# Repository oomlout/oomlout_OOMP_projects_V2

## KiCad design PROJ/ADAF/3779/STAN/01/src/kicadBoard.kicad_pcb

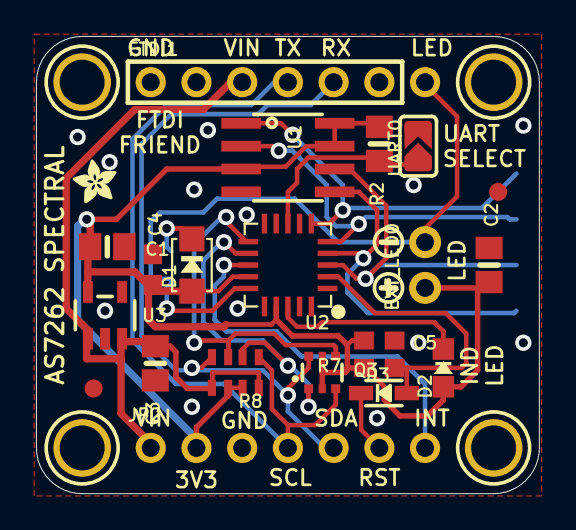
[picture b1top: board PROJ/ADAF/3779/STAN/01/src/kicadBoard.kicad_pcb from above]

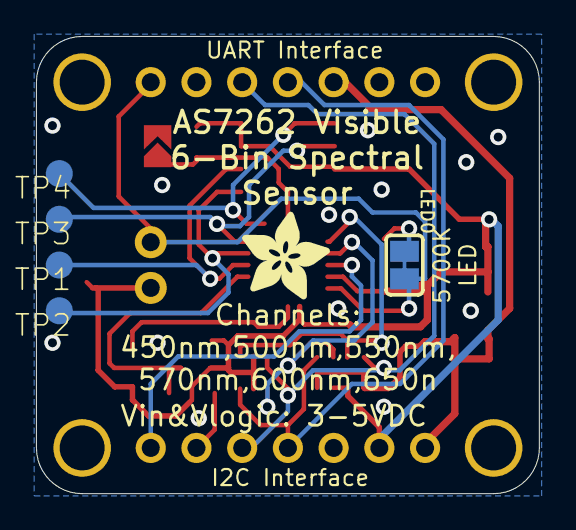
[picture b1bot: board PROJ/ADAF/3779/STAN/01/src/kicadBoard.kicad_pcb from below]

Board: 2 copper layers, 27.9 x 25.4 mm, 34 parts (6 on the bottom side), 18 nets.

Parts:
C1, C2, C3: 10uF; 0805-NO
C4, C5: 0.1uF; 0603-NO
D1: L130-5780001400001; EVERLIGHT_45-21
D2: GREEN; CHIPLED_0805_NOOUTLINE
D3: IN4148; SOD-323
EXT_LED0: 1X02_ROUND
FID2, FID3: FIDUCIAL_1MM
FTDI1: 1X07_ROUND
JP2: 1X07_ROUND
LED0: SOLDERJUMPER_CLOSEDWIRE
Q3: BSS138; SOT363
R2: 10K; 0805-NO
R7: 10K; 0603-NO
R8: 10k; RESPACK_4X0603_NO
TP1, TP2, TP3, TP4: PTR1TP15R; TP15R
U1: AT25SF041-SSHD-B; SOIC8_150MIL
U2: AS7262-BLGT; AS726X_LGA20
U3: MIC5225-3.3; SOT23-5
U$2, U$3, U$22, U$23: MOUNTINGHOLE2.5; MOUNTINGHOLE_2.5_PLATED
U$9: ADAFRUIT_5MM
U$21: ADAFRUIT_2.5MM
U$25: SYMBOL_PLUS
U$26: SYMBOL_MINUS
UART0: SOLDERJUMPER_ARROW_NOPASTE

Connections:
3.3V: C1.1, C2.1, C4.1, C5.1, D1.A, D2.A, EXT_LED0.1, JP2.2, Q3.2, Q3.5, R2.1, R7.2, R8.6, R8.7, U1.3, U1.7, U1.8, U2.14, U2.17, U3.5
BUS_3V: R2.2, U2.8, UART0.1
GND: C1.2, C2.2, C3.2, C4.2, C5.2, FTDI1.1, JP2.3, U1.4, U2.16, U3.2, UART0.2
IND: D2.C, U2.18
INT: JP2.7, U2.13
LED: EXT_LED0.2, FTDI1.7, LED0.2, U2.15
unnamed: D1.K, LED0.1
RESET: D3.C, JP2.6
RST_3V: D3.A, R7.1, U2.2
RX/SCL: FTDI1.4, JP2.4, Q3.3, R8.1
RX/SCL_3V: Q3.4, R8.3, U2.11
SPIF_CS: TP4.TP, U1.1, U2.6
SPIF_MISO: TP3.TP, U1.2, U2.5
SPIF_MOSI: TP2.TP, U1.5, U2.4
SPIF_SCK: TP1.TP, U1.6, U2.3
TX/SDA: FTDI1.5, JP2.5, Q3.6, R8.4
TX/SDA_3V: Q3.1, R8.2, U2.12
VIN: C3.1, FTDI1.3, JP2.1, R8.5, R8.8, U3.1, U3.3

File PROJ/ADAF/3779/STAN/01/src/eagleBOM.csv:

"Part";"Value";"Device";"Package";"Description";"BOM";"TP_SIGNAL_NAME";
"C1";"10uF";"RESISTOR0805_NOOUTLINE";"0805-NO";"Resistors";"";"";
"C2";"10uF";"CAP_CERAMIC0805-NOOUTLINE";"0805-NO";"Ceramic Capacitors";"";"";
"C3";"10uF";"CAP_CERAMIC0805-NOOUTLINE";"0805-NO";"Ceramic Capacitors";"";"";
"C4";"0.1uF";"CAP_CERAMIC0603_NO";"0603-NO";"Ceramic Capacitors";"";"";
"C5";"0.1uF";"CAP_CERAMIC0603_NO";"0603-NO";"Ceramic Capacitors";"";"";
"D1";"L130-5780001400001";"LEDEV45-21";"EVERLIGHT_45-21";"LED";"";"";
"D2";"GREEN";"LED0805_NOOUTLINE";"CHIPLED_0805_NOOUTLINE";"LED";"";"";
"D3";"IN4148";"DIODESOD-323";"SOD-323";"Diode";"";"";
"EXT_LED";"";"HEADER-1X2ROUND";"1X02_ROUND";"PIN HEADER";"";"";
"FID2";"FIDUCIAL_1MM";"FIDUCIAL_1MM";"FIDUCIAL_1MM";"Fiducial Alignment Points";"EXCLUDE";"";
"FID3";"FIDUCIAL_1MM";"FIDUCIAL_1MM";"FIDUCIAL_1MM";"Fiducial Alignment Points";"EXCLUDE";"";
"FTDI1";"";"HEADER-1X7ROUND";"1X07_ROUND";"PIN HEADER";"";"";
"JP2";"";"HEADER-1X7ROUND";"1X07_ROUND";"PIN HEADER";"";"";
"LED";"";"SOLDERJUMPERCLOSED";"SOLDERJUMPER_CLOSEDWIRE";"SMD Solder JUMPER";"";"";
"Q3";"BSS138";"MOSFET-N_DUAL";"SOT363";"Dual N-Channel MOSFET";"";"";
"R2";"10K";"RESISTOR0805_NOOUTLINE";"0805-NO";"Resistors";"";"";
"R7";"10K";"RESISTOR_0603_NOOUT";"0603-NO";"Resistors";"";"";
"R8";"10k";"RESISTOR_4PACK_NO";"RESPACK_4X0603_NO";"Resistor Packs (4 resistors)";"";"";
"TP1";"PTR1TP15R";"PTR1TP15R";"TP15R";"TEST PIN";"";"";
"TP2";"PTR1TP15R";"PTR1TP15R";"TP15R";"TEST PIN";"";"";
"TP3";"PTR1TP15R";"PTR1TP15R";"TP15R";"TEST PIN";"";"";
"TP4";"PTR1TP15R";"PTR1TP15R";"TP15R";"TEST PIN";"";"";
"U$2";"MOUNTINGHOLE2.5";"MOUNTINGHOLE2.5";"MOUNTINGHOLE_2.5_PLATED";"Mounting Hole";"EXCLUDE";"";
"U$3";"MOUNTINGHOLE2.5";"MOUNTINGHOLE2.5";"MOUNTINGHOLE_2.5_PLATED";"Mounting Hole";"EXCLUDE";"";
"U$22";"MOUNTINGHOLE2.5";"MOUNTINGHOLE2.5";"MOUNTINGHOLE_2.5_PLATED";"Mounting Hole";"EXCLUDE";"";
"U$23";"MOUNTINGHOLE2.5";"MOUNTINGHOLE2.5";"MOUNTINGHOLE_2.5_PLATED";"Mounting Hole";"EXCLUDE";"";
"U1";"AT25SF041-SSHD-B";"SPIFLASH_SOIC8";"SOIC8_150MIL";"SOIC8 SPI Flash";"";"";
"U2";"AS7262-BLGT";"AS726X_SPECTRAL";"AS726X_LGA20";"AS726x Spectral Sensor";"";"";
"U3";"MIC5225-3.3";"VREG_SOT23-5";"SOT23-5";"SOT23-5 Fixed Voltage Regulators";"";"";
"UART";"";"SOLDERJUMPER";"SOLDERJUMPER_ARROW_NOPASTE";"SMD Solder JUMPER";"EXCLUDE";"";

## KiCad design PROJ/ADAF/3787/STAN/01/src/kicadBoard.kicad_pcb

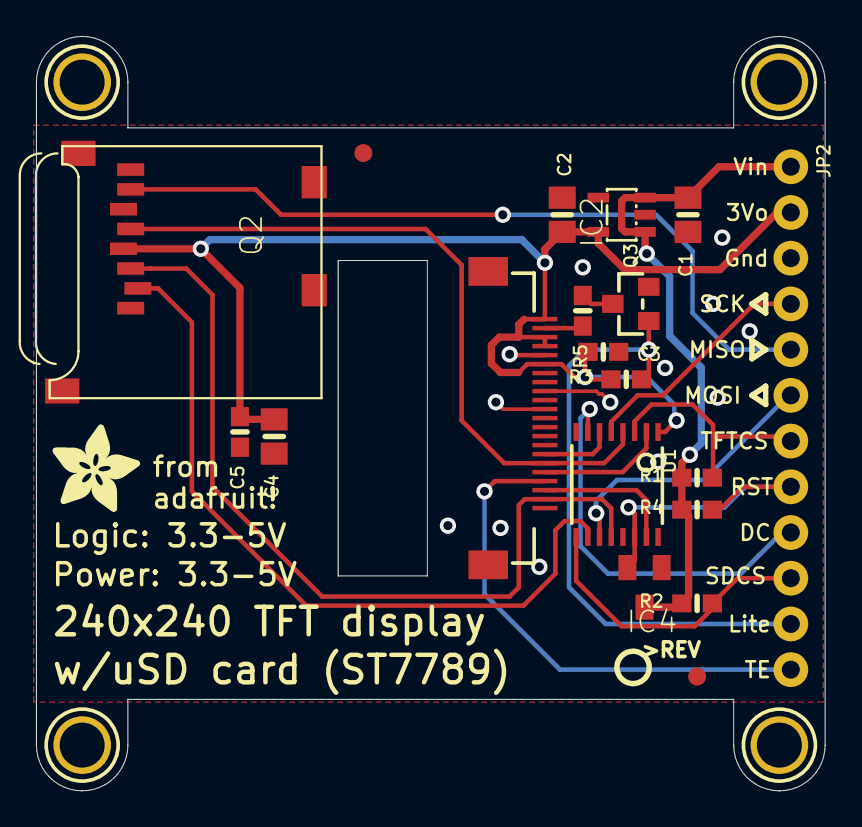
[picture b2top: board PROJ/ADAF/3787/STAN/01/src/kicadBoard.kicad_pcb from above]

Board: 16 copper layers, 43.8 x 41.9 mm, 25 parts (1 on the bottom side), 20 nets.

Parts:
C1, C2, C4: 10uF; 0805-NO
C3, C5: 0.1uF; 0603-NO
IC2: AP2112; SOT23-5L
IC4: APX803-SAG; SOT23
JP2: 1X12_ROUND_76MIL
Q2: MICROSD
Q3: BSS138; SOT23-WIDE
R1, R2, R3, R4: 10K; 0603-NO
R5: 10; 0603-NO
TFT1: DISP_TFT_1.54IN_240X240_22P; TFT_1.54IN_240X240_22PIN
U1: 74HC4050PWR; TSSOP16
U$1: ADAFRUIT_5MM
U$2: PCBFEAT-REV-040
U$4, U$5: FIDUCIAL_1MM
U$7, U$8, U$9, U$10: MOUNTINGHOLE2.5; MOUNTINGHOLE_2.5_PLATED

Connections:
+3V3: C2.1, C3.1, C4.1, C5.1, IC2.5, JP2.2, Q2.4, R3.2, TFT1.1, TFT1.3, TFT1.4, TFT1.6, U1.1
CARDCS: JP2.10, R2.1, U1.9
CARDCS_3V: Q2.2, U1.10
GND: C1.2, C2.2, C3.2, C4.2, C5.2, IC2.2, IC4.1, JP2.3, Q2.6, Q2.MT1, Q2.MT2, Q3.2, TFT1.5, TFT1.7, TFT1.8, TFT1.9, TFT1.10, TFT1.11, TFT1.12, TFT1.13, TFT1.14, TFT1.15, TFT1.22, TFT1.SUPPORT1, TFT1.SUPPORT2, U1.8
LEDK: R5.2, TFT1.2
LITE: JP2.11, Q3.1, R3.1
MISO: JP2.5, Q2.7
MOSI: JP2.6, U1.11
MOSI_3V: Q2.3, TFT1.21, U1.12
unnamed: Q3.3, R5.1
SCK: JP2.4, U1.5
SCK_3V: Q2.5, TFT1.17, U1.4
TE: JP2.12, TFT1.19
TFTCS: JP2.7, R1.1, U1.3
TFTCS_3V: TFT1.18, U1.2
TFTDC: JP2.9, U1.7
TFTDC_3V: TFT1.16, U1.6
TFTRST: IC4.2, JP2.8, R4.1, U1.14
TFTRST_3V: TFT1.20, U1.15
VIN: C1.1, IC2.1, IC2.3, IC4.3, JP2.1, R1.2, R2.2, R4.2

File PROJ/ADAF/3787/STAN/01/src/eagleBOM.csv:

"Part";"Value";"Device";"Package";"Description";"BOM";
"C1";"10uF";"CAP_CERAMIC0805-NOOUTLINE";"0805-NO";"Ceramic Capacitors";"";
"C2";"10uF";"CAP_CERAMIC0805-NOOUTLINE";"0805-NO";"Ceramic Capacitors";"";
"C3";"0.1uF";"CAP_CERAMIC0603_NO";"0603-NO";"Ceramic Capacitors";"";
"C4";"10uF";"CAP_CERAMIC0805-NOOUTLINE";"0805-NO";"Ceramic Capacitors";"";
"C5";"0.1uF";"CAP_CERAMIC0603_NO";"0603-NO";"Ceramic Capacitors";"";
"IC2";"AP2112";"LP298XS";"SOT23-5L";"";"";
"IC4";"APX803-SAG";"AXP083-SAG";"SOT23";"";"";
"JP2";"";"HEADER-1X1276MIL";"1X12_ROUND_76MIL";"";"";
"Q2";"MICROSD";"MICROSD";"MICROSD";"Micro-SD / Transflash card holder with SPI pinout";"";
"Q3";"BSS138";"MOSFET-NWIDE";"SOT23-WIDE";"N-Channel Mosfet";"";
"R1";"10K";"RESISTOR_0603_NOOUT";"0603-NO";"Resistors";"";
"R2";"10K";"RESISTOR_0603_NOOUT";"0603-NO";"Resistors";"";
"R3";"10K";"RESISTOR_0603_NOOUT";"0603-NO";"Resistors";"";
"R4";"10K";"RESISTOR_0603_NOOUT";"0603-NO";"Resistors";"";
"R5";"10";"RESISTOR_0603_NOOUT";"0603-NO";"Resistors";"";
"TFT1";"DISP_TFT_1.54IN_240X240_22P";"DISP_TFT_1.54IN_240X240_22P";"TFT_1.54IN_240X240_22PIN";"";"";
"U$4";"FIDUCIAL_1MM";"FIDUCIAL_1MM";"FIDUCIAL_1MM";"Fiducial Alignment Points";"EXCLUDE";
"U$5";"FIDUCIAL_1MM";"FIDUCIAL_1MM";"FIDUCIAL_1MM";"Fiducial Alignment Points";"EXCLUDE";
"U$7";"MOUNTINGHOLE2.5";"MOUNTINGHOLE2.5";"MOUNTINGHOLE_2.5_PLATED";"Mounting Hole";"EXCLUDE";
"U$8";"MOUNTINGHOLE2.5";"MOUNTINGHOLE2.5";"MOUNTINGHOLE_2.5_PLATED";"Mounting Hole";"EXCLUDE";
"U$9";"MOUNTINGHOLE2.5";"MOUNTINGHOLE2.5";"MOUNTINGHOLE_2.5_PLATED";"Mounting Hole";"EXCLUDE";
"U$10";"MOUNTINGHOLE2.5";"MOUNTINGHOLE2.5";"MOUNTINGHOLE_2.5_PLATED";"Mounting Hole";"EXCLUDE";
"U1";"74HC4050PWR";"74HC4050DTSSOP";"TSSOP16";"6-channel level shifter";"";

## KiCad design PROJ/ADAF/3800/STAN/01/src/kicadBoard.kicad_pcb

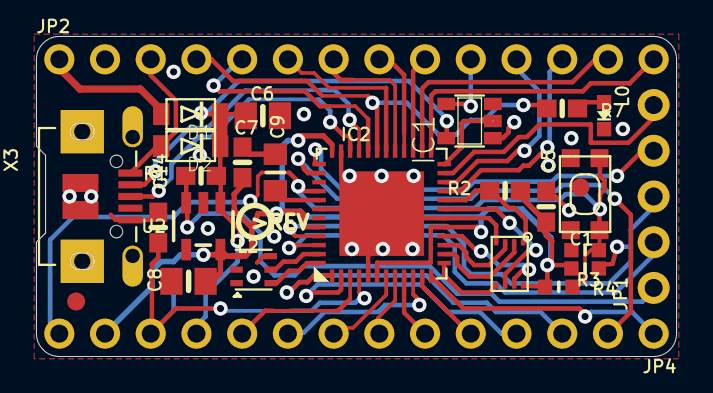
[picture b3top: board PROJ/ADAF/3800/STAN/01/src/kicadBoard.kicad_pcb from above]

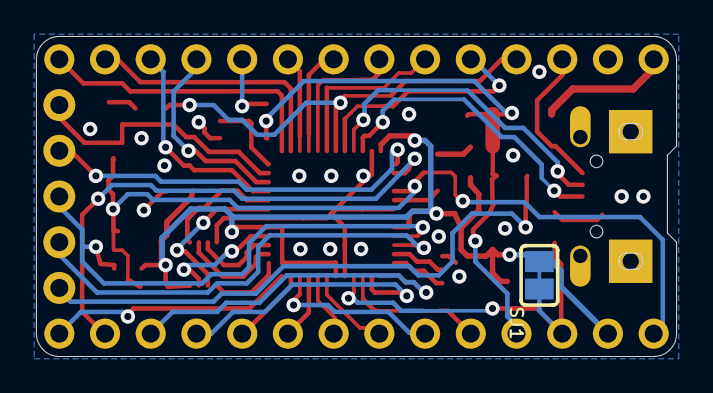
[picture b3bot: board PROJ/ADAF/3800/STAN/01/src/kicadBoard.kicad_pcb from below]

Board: 4 copper layers, 35.6 x 17.8 mm, 31 parts (2 on the bottom side), 46 nets.

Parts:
C1: 1uF; _0603MP
C5, C7, C14: 1uF; 0603-NO
C6, C8: 10µF; 0805-NO
C9: 10uF; _0805MP
D1, D2: MBR120; SOD-123FL
IC1: 74HCT1G125DBV; SOT23-5
IC2: ATSAMD51G_TQFN48; TQFN48_7MM
JP1: 1X05_ROUND_70
JP2, JP4: 1X14_ROUND70
L0: RED; CHIPLED_0603_NOOUTLINE
L2: AP102-2020; APA102_2020
R1, R2: 100k; 0603-NO
R3: 2.2K; _0603MP
R4: 10K; _0603MP
R7: 2.2K; 0603-NO
SJ1: SOLDERJUMPER_CLOSEDWIRE
SW1: SPST_TACT-KMR2; KMR2
U1: GD25x16; USON8
U2: AP2112K-3.3; SOT23-5
U$4: ITSYM4_TOP
U$5: ITSYM4_BOT
U$6: PCBFEAT-REV-040
U$34, U$35: FIDUCIAL_1MM
X3: microUSB; 4UCONN_20329_V2

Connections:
+3V3: C5.1, C7.1, C8.1, IC2.6, IC2.17, IC2.36, IC2.44, JP4.13, L2.3, R2.1, R3.2, R4.1, SJ1.2, U1.8, U2.5
A0: IC2.3, JP4.10
A1: IC2.10, JP4.9
A2: IC2.7, JP4.8
A3: IC2.8, JP4.7
A4: IC2.9, JP4.6
A5: IC2.11, JP4.5
AREF: C14.1, IC2.4, JP4.12, SJ1.1
D2: IC2.12, JP4.1
D3: IC2.37, JP1.4
D4: IC2.23, JP1.5
D5: IC1.2, IC2.24
D5_5V: IC1.4, JP2.10
D7: IC2.27, JP2.9
D9: IC2.28, JP2.8
D10: IC2.29, JP2.7
D11: IC2.30, JP2.6
D12: IC2.32, JP2.5
D13: IC2.31, JP2.4, R7.1
D+: IC2.34, X3.D+
D-: IC2.33, X3.D-
DOTSTAR_CLK: IC2.47, L2.5
DOTSTAR_DATA: IC2.48, L2.6
EN: JP1.1, R1.2, U2.3
GND: C1.1, C5.2, C6.2, C7.2, C8.2, C9.2, C14.2, IC1.1, IC1.3, IC2.5, IC2.18, IC2.35, IC2.42, IC2.THERMAL, JP2.2, L0.C, L2.4, SW1.2, SW1.4, U1.4, U2.2, X3.BASE@1, X3.BASE@2, X3.GND, X3.SPRT@1, X3.SPRT@2, X3.SPRT@3, X3.SPRT@4
MISO: IC2.38, JP4.2
MOSI: IC2.1, JP4.3
unnamed: L0.A, R7.2
QSPI_CS: IC2.20, R2.2, U1.1
QSPI_DATA[0]: IC2.13, U1.5
QSPI_DATA[1]: IC2.14, U1.2
QSPI_DATA[2]: IC2.15, U1.3
QSPI_DATA[3]: IC2.16, U1.7
QSPI_SCK: IC2.19, U1.6
RX_D0: IC2.25, JP2.14
SCK: IC2.2, JP4.4
SCL: IC2.22, JP2.11
SDA: IC2.21, JP2.12
SWCLK: IC2.45, JP1.3, R3.1
SWDIO: IC2.46, JP1.2
TX_D1: IC2.26, JP2.13
VBAT: D1.A, JP2.1
VBUS: D2.A, JP2.3, X3.VBUS
VDDCORE: C9.1, IC2.41
VHI: C6.1, D1.C, D2.C, IC1.5, JP4.11, R1.1, U2.1
~RESET: C1.2, IC2.40, JP4.14, R4.2, SW1.1, SW1.3

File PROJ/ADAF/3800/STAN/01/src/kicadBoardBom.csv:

"Id";"Designator";"Package";"Quantity";"Designation";"Supplier and ref";
1;"JP4,JP2";"1X14_ROUND70";2;"";;;
2;"C5,C7,C14";"0603-NO";3;"1uF";;;
3;"R7";"0603-NO";1;"2.2K";;;
4;"R1,R2";"0603-NO";2;"100k";;;
5;"C1";"_0603MP";1;"1uF";;;
6;"U$4";"ITSYM4_TOP";1;"";;;
7;"D2,D1";"SOD-123FL";2;"MBR120";;;
8;"U2";"SOT23-5";1;"AP2112K-3.3";;;
9;"C8,C6";"0805-NO";2;"10µF";;;
10;"R3";"_0603MP";1;"2.2K";;;
11;"U$6";"PCBFEAT-REV-040";1;"";;;
12;"U$34,U$35";"FIDUCIAL_1MM";2;"FIDUCIAL_1MM";;;
13;"IC2";"TQFN48_7MM";1;"ATSAMD51G_TQFN48";;;
14;"JP1";"1X05_ROUND_70";1;"";;;
15;"R4";"_0603MP";1;"10K";;;
16;"C9";"_0805MP";1;"10uF";;;
17;"L0";"CHIPLED_0603_NOOUTLINE";1;"RED";;;
18;"L2";"APA102_2020";1;"AP102-2020";;;
19;"X3";"4UCONN_20329_V2";1;"microUSB";;;
20;"IC1";"SOT23-5";1;"74HCT1G125DBV";;;
21;"SW1";"KMR2";1;"SPST_TACT-KMR2";;;
22;"U1";"USON8";1;"GD25x16";;;
23;"SJ1";"SOLDERJUMPER_CLOSEDWIRE";1;"";;;
24;"U$5";"ITSYM4_BOT";1;"";;;

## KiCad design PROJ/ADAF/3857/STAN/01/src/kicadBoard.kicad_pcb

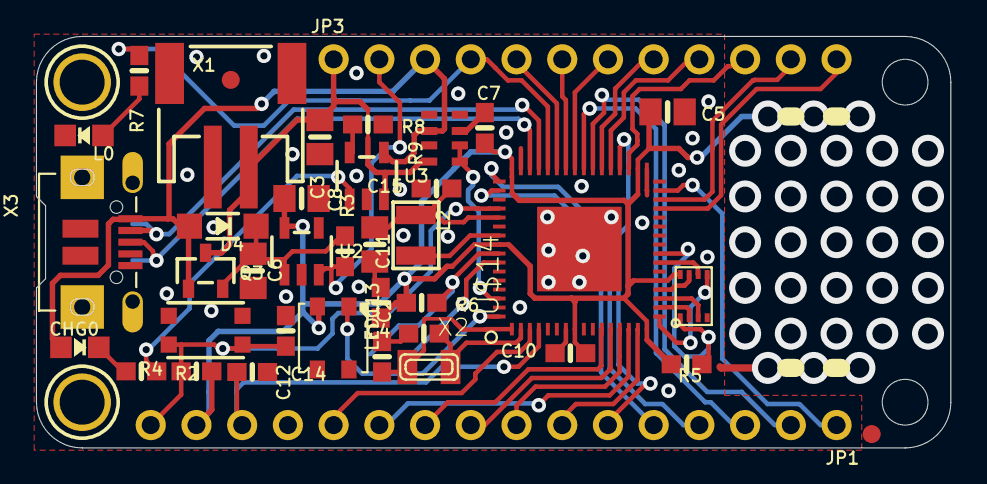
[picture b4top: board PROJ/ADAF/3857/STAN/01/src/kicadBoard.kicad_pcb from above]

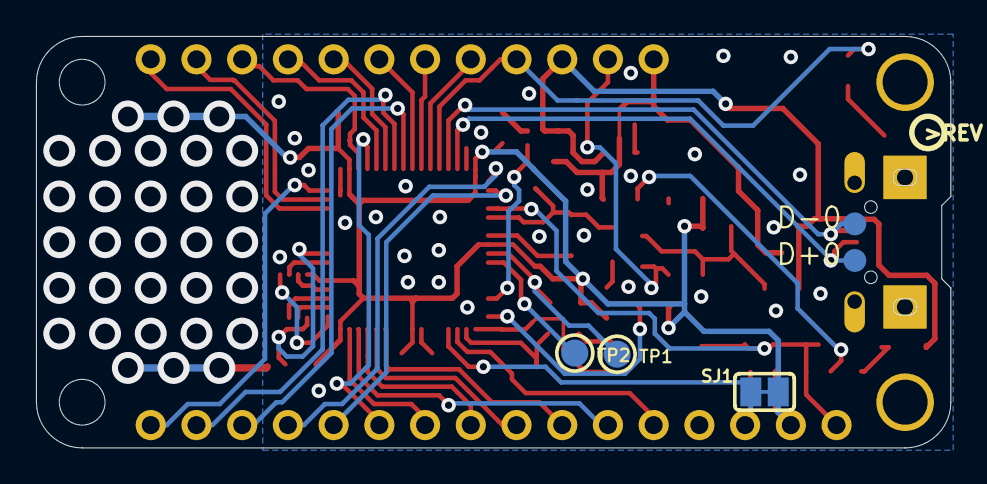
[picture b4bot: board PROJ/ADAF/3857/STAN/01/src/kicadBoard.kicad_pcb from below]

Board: 2 copper layers, 50.8 x 22.9 mm, 51 parts (7 on the bottom side), 49 nets.

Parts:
@HOLE0, @HOLE1: (no value)
C2, C4: 22pF; 0603-NO
C3, C6, C8: 10µF; 0805-NO
C5, C13: 10uF; 0805-NO
C7, C10, C11, C12, C14, C15: 1uF; 0603-NO
CHG0: ORANGE; CHIPLED_0805_NOOUTLINE
D4: MBR120; SOD-123
D+0: TPB1,27; B1,27
D-0: TPB1,27; B1,27
JP1: 1X16_ROUND
JP3: 1X12_ROUND
L0: RED; CHIPLED_0805_NOOUTLINE
L2: 10uH; INDUCTOR_1007
LED1: WS2812B3535; LED3535
Q3: DMG341; SOT23-R
R2: 1K; 0603-NO
R3, R4, R5, R6: 10K; 0603-NO
R7: 2.2K; 0603-NO
R8: 10K\; 0603-NO
R9: 100K; RESPACK_4X0603_NO
SJ1: SOLDERJUMPER_CLOSEDWIRE
SW1: KMR2; BTN_KMR2_4.6X2.8
TP1, TP2: TESTPOINT_ROUND_1.5MM
U1: 2MB Flash; USON8
U2: AP2112-3.3; SOT23-5
U3: MCP73831T-2ACI/OT; SOT23-5
U$5: FEATHERM4_BOT
U$6: FEATHERM4_TOP
U$13: PCBFEAT-REV-040
U$14: ATSAMD51J; PQFN64-1
U$31, U$32: MOUNTINGHOLE2.5; MOUNTINGHOLE_2.5_PLATED
U$34, U$35: FIDUCIAL_1MM
X1: JSTPH; JSTPH2
X2: 32.768; XTAL3215
X3: microUSB; 4UCONN_20329_V2

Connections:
+3V3: C5.1, C7.1, C8.1, C10.1, C11.1, JP1.15, LED1.2, R4.1, R5.2, R6.1, SJ1.2, U1.8, U2.5, U$14.8, U$14.16, U$14.21, U$14.34, U$14.48, U$14.56
A0: JP1.12, U$14.3
A1: JP1.11, U$14.14
A2: JP1.10, U$14.11
A3: JP1.9, U$14.12
A4: JP1.8, U$14.13
A5: JP1.7, U$14.15
AREF: C14.1, JP1.14, SJ1.1, U$14.4
D4: JP1.1, U$14.31
D5: JP3.10, U$14.35
D6: JP3.9, U$14.37
D8_NEOPIX: LED1.1, U$14.64
D9: JP3.8, U$14.38
D10: JP3.7, U$14.41
D11: JP3.6, U$14.42
D12: JP3.5, U$14.43
D13: JP3.4, R7.1, U$14.44
D+: D+0.TP, U$14.46, X3.D+
D-: D-0.TP, U$14.45, X3.D-
EN: JP3.2, R3.1, U2.3
GND: C2.2, C3.2, C4.2, C5.2, C6.2, C7.2, C8.2, C10.2, C11.2, C12.1, C13.2, C14.2, C15.2, JP1.13, L0.C, LED1.4, R8.2, R9.3, R9.7, SW1.B, SW1.B', U1.4, U2.2, U3.2, U$14.7, U$14.22, U$14.33, U$14.47, U$14.54, U$14.EXP, X1.1, X3.BASE@1, X3.BASE@2, X3.GND, X3.SPRT@1, X3.SPRT@2, X3.SPRT@3, X3.SPRT@4
MISO: JP1.4, U$14.49
MOSI: JP1.5, U$14.50
unnamed: CHG0.C, R2.1
unnamed: L0.A, R7.2
unnamed: R2.2, U3.1
unnamed: R8.1, U3.5
unnamed: C2.1, U$14.1, X2.P$1
unnamed: C4.1, U$14.2, X2.P$2
unnamed: L2.P$2, U$14.55
QSPI_CS: R5.1, U1.1, U$14.24
QSPI_DATA[0]: U1.5, U$14.17
QSPI_DATA[1]: U1.2, U$14.18
QSPI_DATA[2]: U1.3, U$14.19
QSPI_DATA[3]: U1.7, U$14.20
QSPI_SCK: U1.6, U$14.23
RX_D0: JP1.3, U$14.40
SCK: JP1.6, U$14.36
SCL: JP3.11, U$14.30
SDA: JP3.12, U$14.29
SWCLK: R6.2, TP1.P$1, U$14.57
SWDIO: TP2.P$1, U$14.58
TX_D1: JP1.2, U$14.39
VBAT: C3.1, JP3.1, Q3.3, R9.8, U3.3, X1.2
VBUS: CHG0.A, D4.A, JP3.3, Q3.1, R9.6, U3.4, X3.VBUS
VDDCORE1: C13.1, C15.1, L2.P$1, U$14.53
VHI: C6.1, D4.C, Q3.2, R3.2, U2.1
V_DIV: R9.1, R9.2, U$14.62
~RESET: C12.2, JP1.16, R4.2, SW1.A, SW1.A', U$14.52

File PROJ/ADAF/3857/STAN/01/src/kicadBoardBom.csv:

"Id";"Designator";"Package";"Quantity";"Designation";"Supplier and ref";
1;"C15,C7,C11,C10,C14,C12";"0603-NO";6;"1uF";;;
2;"C5,C13";"0805-NO";2;"10uF";;;
3;"C2,C4";"0603-NO";2;"22pF";;;
4;"X2";"XTAL3215";1;"32.768";;;
5;"U1";"USON8";1;"2MB Flash";;;
6;"R4,R5,R6,R3";"0603-NO";4;"10K";;;
7;"R7";"0603-NO";1;"2.2K";;;
8;"X1";"JSTPH2";1;"JSTPH";;;
9;"JP3";"1X12_ROUND";1;"";;;
10;"U$6";"FEATHERM4_TOP";1;"";;;
11;"R8";"0603-NO";1;"10K\";;;
12;"L0";"CHIPLED_0805_NOOUTLINE";1;"RED";;;
13;"U$14";"PQFN64-1";1;"ATSAMD51J";;;
14;"JP1";"1X16_ROUND";1;"";;;
15;"L2";"INDUCTOR_1007";1;"10uH";;;
16;"R9";"RESPACK_4X0603_NO";1;"100K";;;
17;"SW1";"BTN_KMR2_4.6X2.8";1;"KMR2";;;
18;"@HOLE1,@HOLE0";"";2;"";;;
19;"U$35,U$34";"FIDUCIAL_1MM";2;"FIDUCIAL_1MM";;;
20;"C6,C3,C8";"0805-NO";3;"10µF";;;
21;"X3";"4UCONN_20329_V2";1;"microUSB";;;
22;"U3";"SOT23-5";1;"MCP73831T-2ACI/OT";;;
23;"U$31,U$32";"MOUNTINGHOLE_2.5_PLATED";2;"MOUNTINGHOLE2.5";;;
24;"Q3";"SOT23-R";1;"DMG341";;;
25;"LED1";"LED3535";1;"WS2812B3535";;;
26;"U2";"SOT23-5";1;"AP2112-3.3";;;
27;"R2";"0603-NO";1;"1K";;;
28;"D4";"SOD-123";1;"MBR120";;;
29;"CHG0";"CHIPLED_0805_NOOUTLINE";1;"ORANGE";;;
30;"TP2,TP1";"TESTPOINT_ROUND_1.5MM";2;"";;;
31;"SJ1";"SOLDERJUMPER_CLOSEDWIRE";1;"";;;
32;"U$5";"FEATHERM4_BOT";1;"";;;
33;"D-0,D+0";"B1,27";2;"TPB1,27";;;
34;"U$13";"PCBFEAT-REV-040";1;"";;;

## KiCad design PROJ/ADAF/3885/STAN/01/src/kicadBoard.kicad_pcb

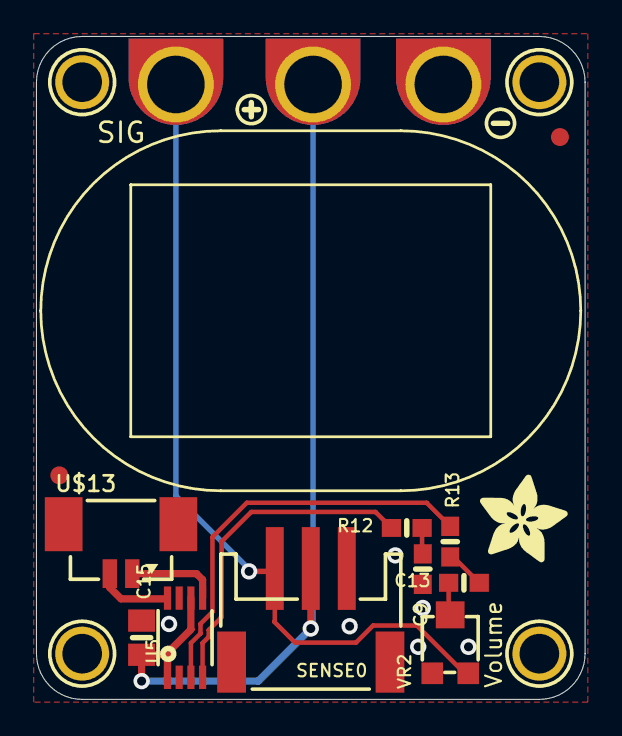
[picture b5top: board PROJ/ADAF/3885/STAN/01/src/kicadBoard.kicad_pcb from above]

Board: 2 copper layers, 30.5 x 36.8 mm, 23 parts (1 on the bottom side), 10 nets.

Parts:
C9, C13: 1uF; 0603-NO
C15: 10uF; 0805-NO
FID1, FID2: FIDUCIAL_1MM
R12, R13: 100; 0603-NO
SENSE0: JST PH 3; JSTPH3
TP1, TP2, TP3: SEWTAPPCB_ALLIGATOR; PCB_ALLI
U5: PAM8302AASCR; MSOP8_0.65MM
U$1: SPEAKER_OVAL8OHM
U$3: ADAFRUIT_5MM
U$4: STEMMA_SPEAKER
U$5: SYMBOL_MINUS
U$6: SYMBOL_PLUS
U$9, U$10, U$11, U$12: MOUNTINGHOLE2.0; MOUNTINGHOLE_2.0_PLATED
U$13: CON_MOLEX_2P; 53398-0271
VR2: 10K trim; TRIMPOT_BOURNS_3303W

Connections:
GND: C9.2, C15.2, SENSE0.1, TP1.P$1, U5.7, VR2.1
unnamed: R12.2, U5.4
unnamed: R13.2, U5.3
unnamed: C9.1, R12.1
unnamed: C13.1, R13.1
unnamed: C13.2, VR2.2
SIG: SENSE0.3, TP3.P$1, VR2.3
SPKR+: U5.5, U$13.1
SPKR-: U5.8, U$13.2
VDD: C15.1, SENSE0.2, TP2.P$1, U5.1, U5.6

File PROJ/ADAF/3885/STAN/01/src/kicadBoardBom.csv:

"Id";"Designator";"Package";"Quantity";"Designation";"Supplier and ref";
1;"U$1";"SPEAKER_OVAL8OHM";1;"";;;
2;"C15";"0805-NO";1;"10uF";;;
3;"U$6";"SYMBOL_PLUS";1;"";;;
4;"U$9,U$10,U$12,U$11";"MOUNTINGHOLE_2.0_PLATED";4;"MOUNTINGHOLE2.0";;;
5;"FID1,FID2";"FIDUCIAL_1MM";2;"FIDUCIAL_1MM";;;
6;"R13,R12";"0603-NO";2;"100";;;
7;"U$5";"SYMBOL_MINUS";1;"";;;
8;"C13,C9";"0603-NO";2;"1uF";;;
9;"SENSE0";"JSTPH3";1;"JST PH 3";;;
10;"TP3,TP1,TP2";"PCB_ALLI";3;"SEWTAPPCB_ALLIGATOR";;;
11;"U$13";"53398-0271";1;"CON_MOLEX_2P";;;
12;"U$3";"ADAFRUIT_5MM";1;"";;;
13;"VR2";"TRIMPOT_BOURNS_3303W";1;"10K trim";;;
14;"U5";"MSOP8_0.65MM";1;"PAM8302AASCR";;;
15;"U$4";"STEMMA_SPEAKER";1;"";;;

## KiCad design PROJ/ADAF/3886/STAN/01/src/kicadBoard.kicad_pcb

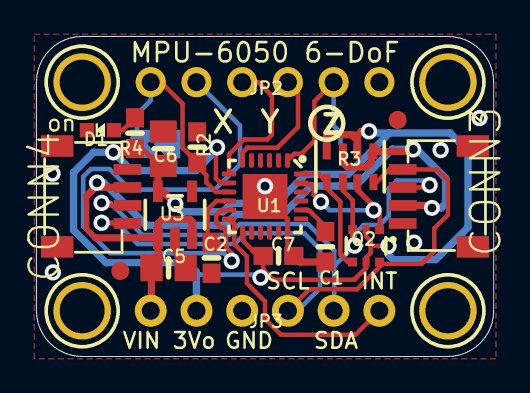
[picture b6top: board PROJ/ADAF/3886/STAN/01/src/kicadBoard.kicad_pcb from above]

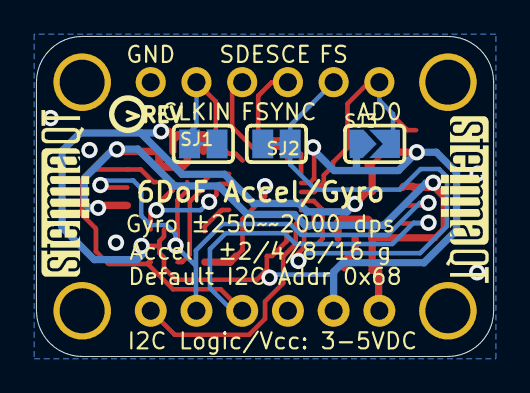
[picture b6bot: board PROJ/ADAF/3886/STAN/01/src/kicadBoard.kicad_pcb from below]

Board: 2 copper layers, 25.4 x 17.8 mm, 28 parts (6 on the bottom side), 16 nets.

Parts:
C1: 2.2nF; 0603-NO
C2, C7: 0.1uF; 0603-NO
C5, C6: 10uF; 0805-NO
CONN3, CONN4: STEMMA_I2C_QT; JST_SH4
D1: GREEN; CHIPLED_0603_NOOUTLINE
FID3, FID4: FIDUCIAL_1MM
JP2: 1X06_ROUND
JP3: 1X06_ROUND_70
Q2: BSS138; SOT363
R2, R4: 10K; 0603-NO
R3: 10K; RESPACK_4X0603
SJ1: CLKIN; SOLDERJUMPER_CLOSEDWIRE
SJ2: FSYNC; SOLDERJUMPER_CLOSEDWIRE
SJ3: SOLDERJUMPER_ARROW_NOPASTE
U1: MPU-6050; QFN24_4MM_SMSC
U3: AP2112K-3.3; SOT23-5
U$39, U$40, U$42, U$43: MOUNTINGHOLE2.5; MOUNTINGHOLE_2.5_PLATED
U$46: PCBFEAT-REV-040
U$47, U$48: STEMMAQT

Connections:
3.3V: C6.1, C7.1, JP3.2, Q2.2, Q2.5, R3.2, R3.4, R4.1, SJ3.1, U1.8, U1.13, U3.5
AD0: JP2.1, R2.1, SJ3.2, U1.9
CLKIN: JP2.5, SJ1.2, U1.1
CPOUT: C1.1, U1.20
FSYNC_IN: JP2.2, SJ2.2, U1.11
GND: C1.2, C2.2, C5.2, C6.2, C7.2, CONN3.1, CONN4.1, D1.C, JP2.6, JP3.3, R2.2, SJ1.1, SJ2.1, U1.18, U1.THERM, U3.2
INT: JP3.6, U1.12
unnamed: D1.A, R4.2
REGOUT: C2.1, U1.10
SCL: CONN3.4, CONN4.4, JP3.4, Q2.6, R3.8
SCL_3V: Q2.1, R3.7, U1.23
SCL_EXT: JP2.3, U1.7
SDA: CONN3.3, CONN4.3, JP3.5, Q2.3, R3.6
SDA_3V: Q2.4, R3.5, U1.24
SDA_EXT: JP2.4, U1.6
VCC: C5.1, CONN3.2, CONN4.2, JP3.1, R3.1, R3.3, U3.1, U3.3

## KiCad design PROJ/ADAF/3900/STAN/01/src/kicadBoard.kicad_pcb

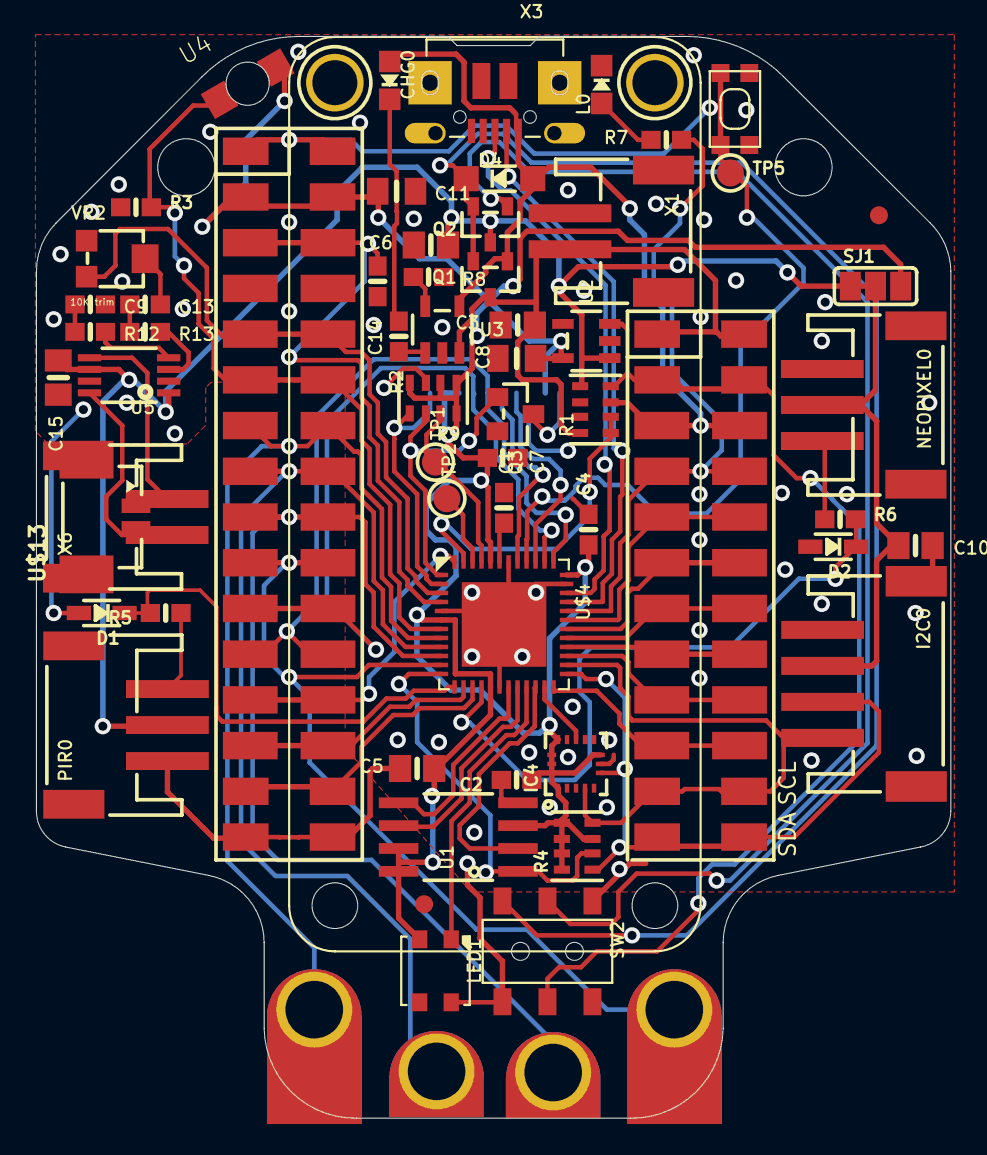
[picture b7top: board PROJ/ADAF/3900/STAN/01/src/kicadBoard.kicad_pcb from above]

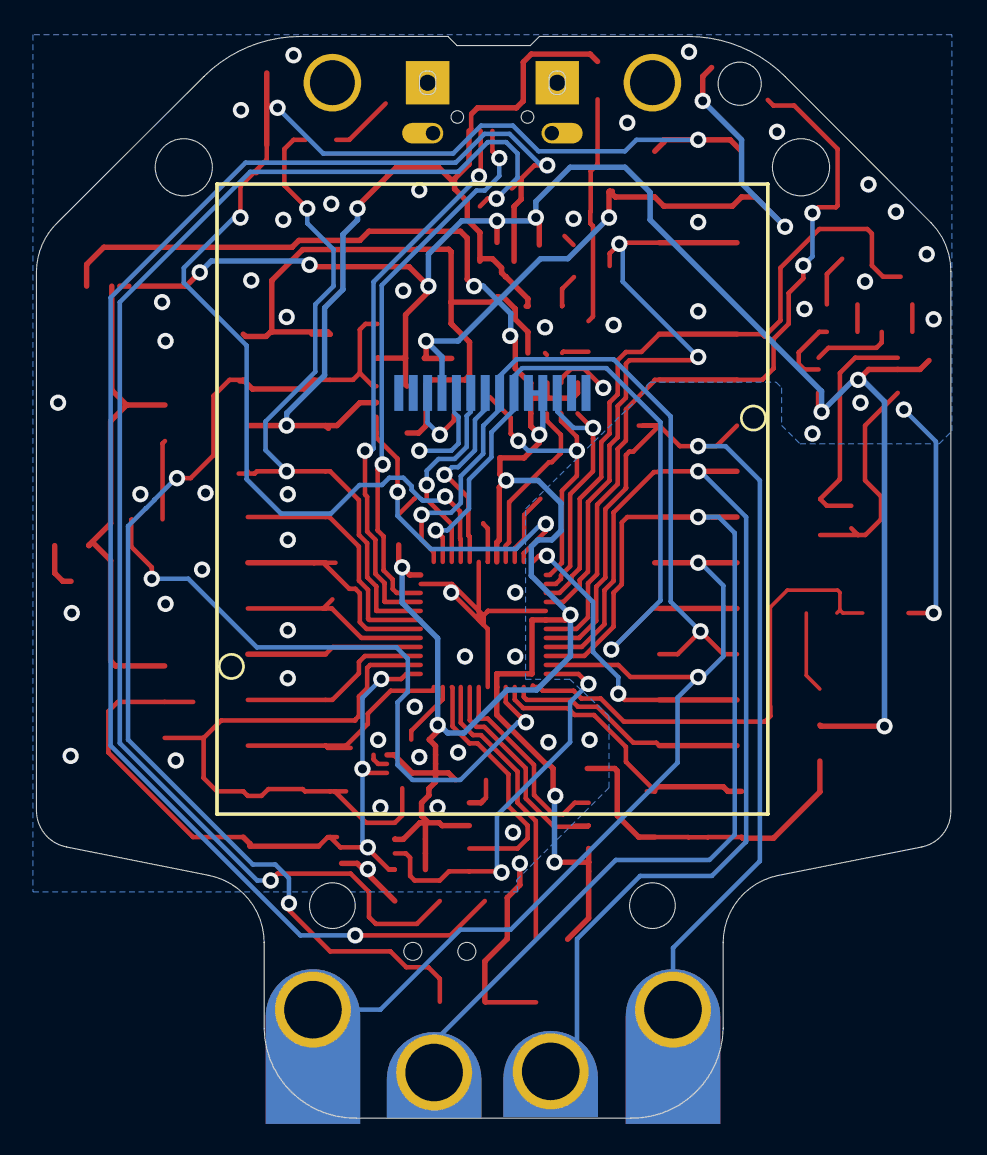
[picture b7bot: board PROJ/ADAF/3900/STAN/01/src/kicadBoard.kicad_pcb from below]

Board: 2 copper layers, 50.8 x 60.1 mm, 71 parts (2 on the bottom side), 63 nets.

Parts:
@HOLE0, @HOLE1, @HOLE2, @HOLE3: (no value)
C1, C2, C4, C7, C9, C13, C14: 1uF; 0603-NO
C3, C6: 10µF; 0805-NO
C5, C10, C15: 10uF; 0805-NO
C8: 10µF; 0805_10MGAP
C11: 10uF; 0805_10MGAP
CHG0: ORANGE; CHIPLED_0805_NOOUTLINE
D1, D2: 3.6V; SOD-323
D4: MBR120; SOD-123
I2C0: JST PH 4; JSTPH4
IC4: LIS3DH; LGA16_3X3MM
L0: RED; CHIPLED_0805_NOOUTLINE
LED1: WS2812B3535; LED3535
MS1: FEATHERWING_SMTDUALNOHOLES; FEATHERWING_SMT_NOHOLES
NEOPIXEL0: JST PH 3; JSTPH3
PIR0: JST PH 3; JSTPH3
Q1, Q2: DMG341; SOT23-R
Q3: BSS138; SOT23-WIDE
R1: 100K; RESPACK_4X0603
R2, R5, R6: 1K; 0603-NO
R3, R8: 10K; 0603-NO
R4, R9: 10K; RESPACK_4X0603
R7: 2.2K; 0603-NO
R12, R13: 100; 0603-NO
SJ1: SOLDERJUMPER_2WAY_OPEN_NOPASTE
SW1: SPST_TACT-KMR2; KMR2
SW2: Slide Switch; EG1390
TFT0: DISP_LCD_ST7735_1.44IN; TFT_1.44IN_128_128
TP1, TP2, TP5: TESTPOINT_ROUND_1.5MM
TP3, TP29: SEWTAP_ALLILONG; PCB_ALLI_LONG
TP4, TP28: SEWTAPPCB_ALLIGATOR; PCB_ALLI
U1: 2MB Flash; SOIC8_208MIL
U2: AP2112-3.3; SOT23-5
U3: MCP73831T-2ACI/OT; SOT23-5
U4: ALS-PT21; ALS-PT26-21C
U5: PAM8302AASCR; MSOP8_0.65MM
U$4: ATSAMD21G18_QFN; TQFN48_7MM
U$8: HALLOWING_BACK
U$12: HALLOWING_FRONT
U$13: CON_MOLEX_2P; 53398-0271
U$31, U$32: MOUNTINGHOLE2.5; MOUNTINGHOLE_2.5_PLATED
U$34, U$35: FIDUCIAL_1MM
VR2: 10K trim; TRIMPOT_BOURNS_3303W
X1: JSTPH; JSTPH2
X3: microUSB; 4UCONN_20329_V2
X6: CON_JST_PH_2PIN_MTPH2; JSTPH2

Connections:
+3V3: C2.1, C4.1, C5.1, C7.1, C8.1, C11.1, IC4.1, IC4.8, IC4.13, IC4.14, IC4.15, IC4.16, LED1.2, MS1.2, MS1.2', R4.3, R4.5, R4.6, R4.7, R4.8, R9.1, R9.2, R9.4, R9.8, SJ1.3, TFT0.4, TFT0.10, TFT0.11, U1.3, U1.7, U1.8, U2.5, U4.2_C, U$4.6, U$4.17, U$4.36, U$4.44
A0: MS1.5, MS1.5', U$4.3, VR2.3
A1: MS1.6, MS1.6', R3.2, U4.1_E, U$4.7
A2: MS1.7, MS1.7', TP3.P$1, U$4.8
A3: MS1.8, MS1.8', TP4.P$1, U$4.9
A4: MS1.9, MS1.9', TP28.P$1, U$4.10
A5: MS1.10, MS1.10', TP29.P$1, U$4.11
AREF: C14.1, MS1.3, MS1.3', U$4.4
BACKLITE: Q3.1, R9.6, U$4.1
CHG_LED: R2.2, U3.1
CHG_RATE: R8.1, U3.5
D2: IC4.11, U$4.23
D3: D2.C, R6.2, U$4.16
D4: D1.C, R5.2, U$4.13
D5: MS1.19, MS1.19', U$4.24
D6: MS1.20, MS1.20', U$4.27
D8_NEOPIX: LED1.1, U$4.21
D9: MS1.21, MS1.21', U$4.28
D10: MS1.22, MS1.22', U$4.29
D11: MS1.23, MS1.23', U$4.30
D12: MS1.24, MS1.24', U$4.31
D13: MS1.25, MS1.25', R7.1, U$4.32
D+: U$4.34, X3.D+
D-: U$4.33, X3.D-
EN: MS1.27, MS1.27', R1.4, SW2.P1, U2.3
FLASHMISO: U1.2, U$4.22
FLASHMOSI: U1.5, U$4.19
FLASHSCK: U1.6, U$4.20
FLASH_CS: R4.2, U1.1, U$4.12
GND: C1.2, C2.2, C3.2, C4.2, C5.2, C6.2, C7.2, C8.2, C9.2, C10.2, C11.2, C14.2, C15.2, D1.A, D2.A, I2C0.1, I2C0.NC1, I2C0.NC2, IC4.5, IC4.7, IC4.10, IC4.12, L0.C, LED1.4, MS1.4, MS1.4', MS1.16, MS1.16', NEOPIXEL0.1, PIR0.1, Q3.2, R1.6, R1.7, R3.1, R8.2, R9.3, SW1.2, SW1.4, SW2.O2, SW2.S1, TFT0.1, TFT0.2, TFT0.5, TFT0.13, TFT0.14, U1.4, U2.2, U3.2, U5.7, U$4.5, U$4.18, U$4.35, U$4.42, U$4.THERMAL, VR2.1, X1.1, X3.BASE@1, X3.BASE@2, X3.GND, X3.SPRT@1, X3.SPRT@2, X3.SPRT@3, X3.SPRT@4
MISO: MS1.13, MS1.13', U$4.48
MOSI: MS1.12, MS1.12', TFT0.8, U$4.37
unnamed: CHG0.C, R2.1
unnamed: L0.A, R7.2
unnamed: Q3.3, TFT0.3
unnamed: D4.C, Q1.2, Q2.2, SW2.S2
unnamed: R12.2, U5.4
unnamed: R13.2, U5.3
unnamed: C9.1, R12.1
unnamed: C13.1, R13.1
unnamed: C13.2, VR2.2
NEOPIXELOUT: NEOPIXEL0.3, R6.1
ON/OFF: Q2.1, SW2.P2
RX: MS1.14, MS1.14', U$4.14
SCK: MS1.11, MS1.11', TFT0.9, U$4.38
SCL: I2C0.4, IC4.4, MS1.18, MS1.18', R4.4, U$4.26
SDA: I2C0.3, IC4.6, MS1.17, MS1.17', R4.1, U$4.25
SENSORIN: PIR0.3, R5.1
SPKR+: U5.5, U$13.1, X6.2
SPKR-: U5.8, U$13.2, X6.1
SWCLK: R9.7, TP1.P$1, U$4.45
SWDIO: TP2.P$1, U$4.46
TFT_CS: R9.5, TFT0.12, U$4.2
TFT_DC: TFT0.7, U$4.41
TFT_RESET: TFT0.6, U$4.39
TX: MS1.15, MS1.15', U$4.15
V+: C6.1, C15.1, PIR0.2, Q2.3, R1.5, SJ1.1, U2.1, U5.1, U5.6
VBAT: C3.1, MS1.28, MS1.28', Q1.3, R1.8, U3.3, X1.2
VBATT: R1.1, R1.2, U$4.47
VBUS: CHG0.A, D4.A, MS1.26, MS1.26', Q1.1, R1.3, U3.4, X3.VBUS
VCC: C10.1, I2C0.2, NEOPIXEL0.2, SJ1.2
VDDCORE: C1.1, U$4.43
~RESET: MS1.1, MS1.1', SW1.1, SW1.3, TP5.P$1, U$4.40
